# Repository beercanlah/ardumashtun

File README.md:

Ardumashtun
===========

Ardumashtun, an Arduino controlled recirculating mashtun. 

Do you want to improve your home brewing? This projects contains all you need to turn a water heater into a recirculating mash tun. You can find
[more info about our recirculating mash tun](http://beercanlah.com/?page_id=49)
on the blog [beercanlah.com](http://beercanlah.com/).
Here we develop the hard and software that we use to improve our nano brewery.

This repositories contains software for the Arduino. We also provide the eagle cad design design files for the hardware.

Software
------------

We have two different versions of the Arduino sketch that runs our software. One intended for use with an Arduino Uno, and one for use with an Arduino Yun.
When using the Uno you control your mashtun via USB, while the Yun enables you to control your mashtun via the browser.

You can also take a look at the app used for controlling the Uno based mash tun, [kivybrew](https://github.com/beercanlah/kivybrew), and the one controlling the Yun based mash tun, [flapibrew](https://github.com/beercanlah/flapibrew).

Hardware
-------------
Version one of the Ardumashtun hardware is a custom Arduino shield intended to be fabricated by a PCB mill. Recently we have started to migrate towards [Seeedstudios](http://www.seeedstudio.com/) PCB and PCBA service.  We have a running prototype board that only uses parts from the Open Parts Library, so that it can be manufactured using Seeedstudios Fusion PCBA.

License
----------

Unless specifically stated otherwise, everything is licensed under the MIT license, for more information see
LICENSE.txt.

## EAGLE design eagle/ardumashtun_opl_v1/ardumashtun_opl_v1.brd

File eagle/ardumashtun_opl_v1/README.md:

Overview
--------

ardumashtun_opl_v1 is the first attempt to build the mash tun controller using the PCBA service by seeedstudio. 
It works, there are however improvements which we might make in a future version.

Possible Improvements
---------------------

* Label pin header on silk screen
* Add voltage divider on digital pin 0 for use as 3.3 V serial

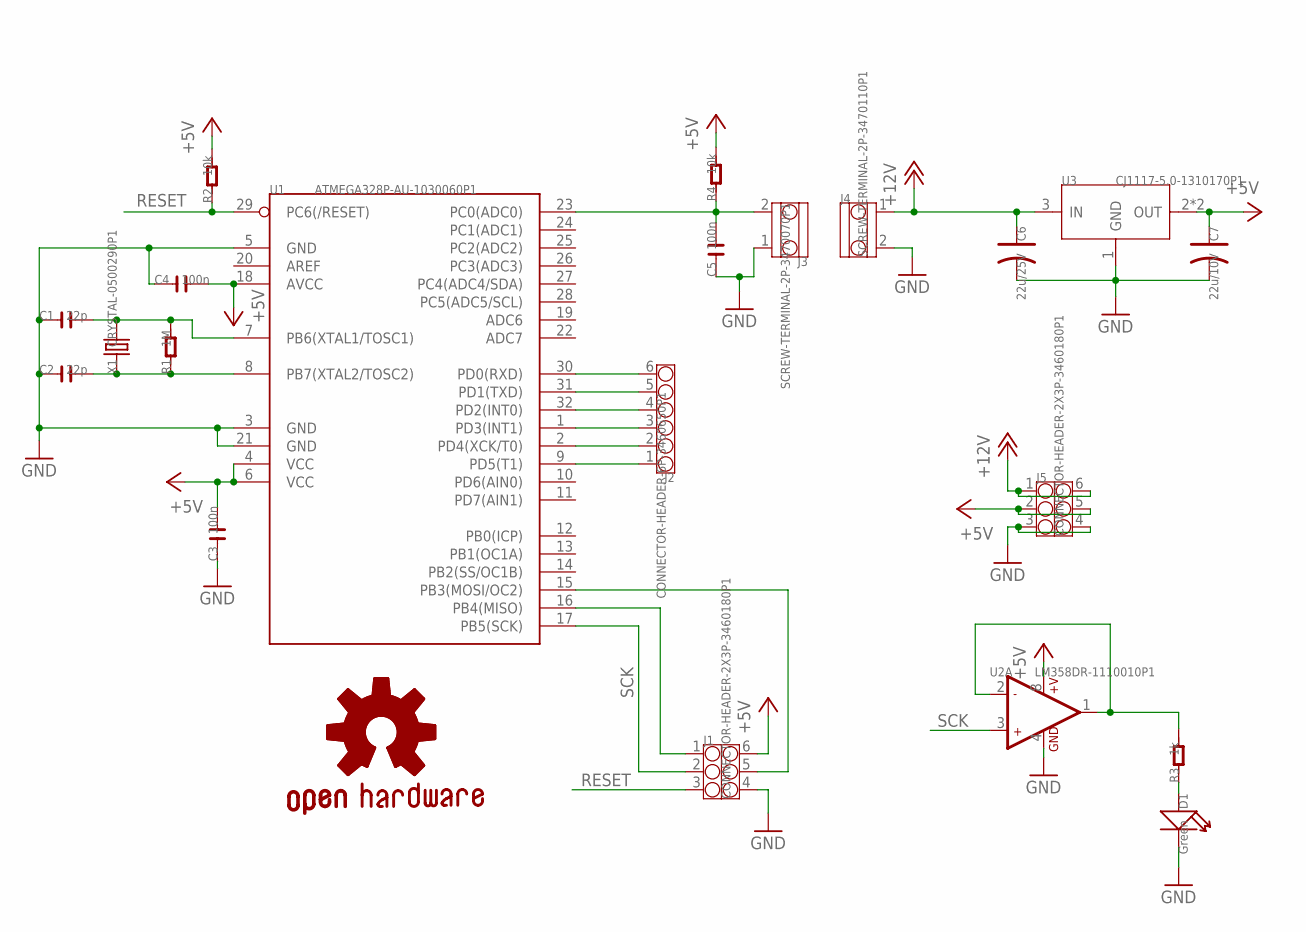
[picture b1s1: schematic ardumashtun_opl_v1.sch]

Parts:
C1, C2: 22p; C0603
C3, C4, C5: 100n; C0603
C6: 22u/25V; AVX-C
C7: 22u/10V; AVX-B
D1: Green; LED0603
GOLD_ORB_SM1: OSHWLOGO_GOLD_ORB_SM; OSHW2
J1, J5: CONNECTOR-HEADER-2X3P-3460180P1; 2X3P-2.54-2.54-11.6-3.0-BLACK-MALE
J2: CONNECTOR-HEADER-6P-3460650P1; 1X6P-2.54-2.54-11.6-3.0-BLACK-MALE
J3: SCREW-TERMINAL-2P-3470070P1; 2P-3.5
J4: SCREW-TERMINAL-2P-3470110P1; 2P-5.0
R1: 1M; R0603
R2, R4: 10k; R0603
R3: 1k; R0603
U1: ATMEGA328P-AU-1030060P1; TQFP32
U2: LM358DR-1110010P1; SOIC8
U3: CJ1117-5.0-1310170P1; SOT223
X1: CRYSTAL-0500290P1; 2P-SMD-5.0X3.2

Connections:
+5V: C3.2, C4.2, C7.+ (1), J1.6, J5.2, J5.5, R2.2, R4.2, U1.4 (VCC), U1.6 (VCC), U1.18 (AVCC), U2.8 (+V), U3.2 (OUT), U3.TER (OUT)
+12V: C6.+ (1), J4.1, J5.1, J5.6, U3.3 (IN)
GND: C1.1, C2.1, C3.1, C4.1, C5.1, C6.- (2), C7.- (2), D1.-, J1.4, J3.1, J4.2, J5.3, J5.4, U1.3 (GND), U1.5 (GND), U1.21 (GND), U2.4 (GND), U3.1 (GND)
unnamed: C1.2, R1.2, U1.7 (PB6(XTAL1/TOSC1)), X1.2
unnamed: C2.2, R1.1, U1.8 (PB7(XTAL2/TOSC2)), X1.1
unnamed: R3.2, U2.1 (OUT1), U2.2 (-IN1)
unnamed: J1.1, U1.16 (PB4(MISO))
unnamed: J1.5, U1.15 (PB3(MOSI/OC2))
unnamed: D1.+, R3.1
unnamed: J2.6, U1.30 (PD0(RXD))
unnamed: J2.5, U1.31 (PD1(TXD))
unnamed: J2.4, U1.32 (PD2(INT0))
unnamed: J2.3, U1.1 (PD3(INT1))
unnamed: J2.2, U1.2 (PD4(XCK/T0))
unnamed: J2.1, U1.9 (PD5(T1))
unnamed: C5.2, J3.2, R4.1, U1.23 (PC0(ADC0))
RESET: J1.3, R2.1, U1.29 (PC6(/RESET))
SCK: J1.2, U1.17 (PB5(SCK)), U2.3 (+IN1)

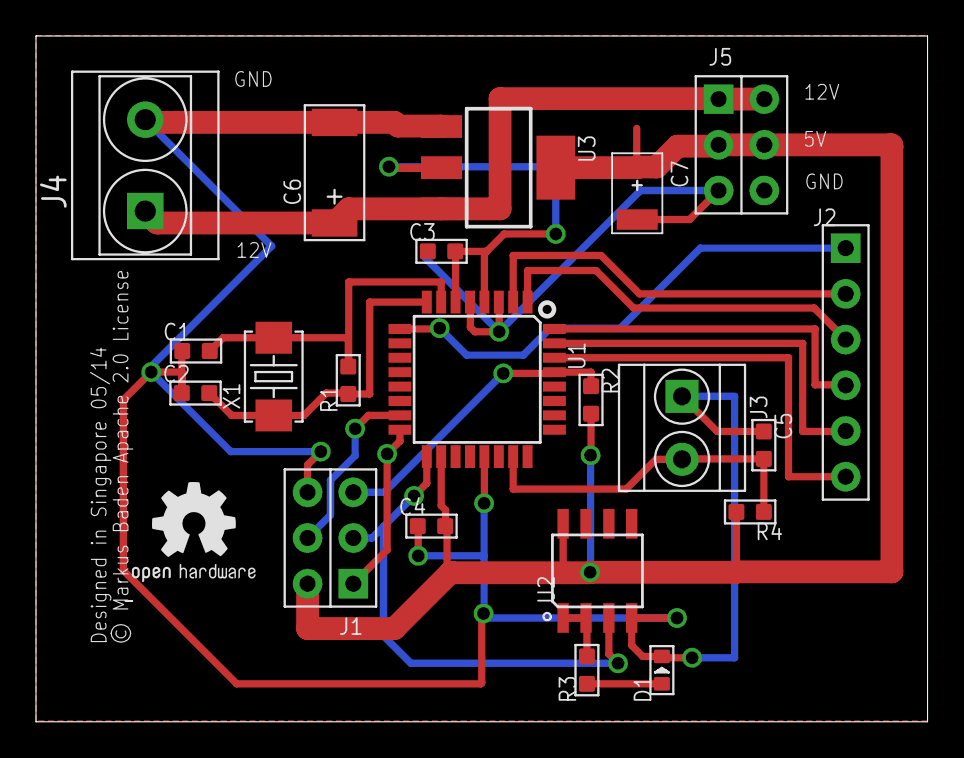
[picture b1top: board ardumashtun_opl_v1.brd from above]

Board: 2 copper layers, 49.5 x 38.1 mm, 22 parts (0 on the bottom side), 18 nets.

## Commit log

2012-01-14 First sketch of zeromq wrapper for serial, that will handle talking to the Arduino
2012-01-22 First version of brew kettle firmware
    Will be based on command parsing since I could not get firmata
    to read analog inputs.
2012-01-22 Pump turns on and off via serial
    Finally got some sort of communications going!
2012-01-23 First script of monitoring temperature committed
2012-01-23 Started class for brew kettle
2012-01-23 Script to monitor temperature now works
2012-01-23 Brew kettle class now controls pump as well
    Monitor temperature script will be used for PID tuning
2012-01-23 refactored echo of readlines
2012-01-23 Monitor temperature script as used for heating measurement
2012-01-23 Have added script to plot data
    Run this in a seperate IPython in order to get
    visual check on things.
2012-01-23 Implemented dutycycle heating
2012-01-23 Further work on duty cycle mode, rewrote brewkettle to parse commands a bit more intelligently. Experimenting with dutycycle mode
2012-01-24 Added way to parse messages using << and defined statements
    Somehow things keep crashing if i put serial inside the if statement...
2012-01-24 Rewrote some of the serial logging, still keeps crashing when serial is inside if statement
2012-01-24 Changed temperature and dutyCycle to be double so that they are compatible with the PID library
2012-01-24 Seems I run out of sram. Commented a lot of log messages. Now can set PID on of
2012-01-24 Added set pid on off to brewekettle.py
2012-01-24 fixed pid on off message cmd id
2012-01-24 Mistake in changing set pid on off cmd id, were correct
2012-01-24 fixed measuretemperature now, void and sets global variabl, error because declared as int
2012-01-24 removed conflicting error messages
2012-01-24 Added setpoint and dutycycle to script
2012-01-24 added function to get input ouput and setpoint
2012-01-24 added input ouput setpoint
2012-01-26 Played some mor ewith zeromq
2012-01-26 Added change setpoint message
2012-01-26 Played with PID parameters, as used for brew
2012-01-26 Added log messages
2012-01-26 arduino sketch as for brew
2012-01-26 brewkettle as for brew
2012-01-26 monitor temperature as for brew
2012-01-26 Removed zeromq files, now in zeromq branch
2012-01-26 Started traits based UI. BrewKettle now inherits from HasTraits
2012-01-26 Setpoint and temperature now default to NaN
2012-01-26 Basic WX App that periodically checks for data implemented
    Taken from https://github.com/enthought/chaco/blob/master/examples/demo/
    advanced/data_stream.py Still closes rather abruptly on exit
2012-01-26 Timer now based on pyface. No more wx, all traitsui based.
2012-01-26 Dummy serial no puts out temperature for testing the app
2012-01-26 Plot of temperature works, after fixing bug in EPD 7.2, see
    https://github.com/enthought/chaco/commit/
    2cb4fd235b928d737b3c244942f8e2e85aa4270d
    and
    https://mail.enthought.com/pipermail/enthought-dev/2012-January/030489.html
2012-01-27 Added timestamp to status message and newly renamed GETALL message
2012-01-27 brewkettle works with new status message
2012-01-27 Reduced timeout in serial communication
2012-01-27 exit from kettle when closing app
2012-01-27 Time now in seconds
2012-01-27 Update the plot manually now works, need to clean py file a lot though
2012-01-27 Cleaned up imports added zoom tool, drawing both at the same time works limits are wrong though
2012-01-27 stopped playing around with overlay plot, can't scale axis... so be it
2012-01-27 Tweaking appearance of views
2012-01-27 Added PID mode flag to get all
2012-01-27 Changed stupid naming getGETALL to getall
2012-01-27 Refactored turning pump on and pump off into seperate function
2012-01-27 Added pump is on flag to get all message
2012-01-27 Added dutycycle and temperature to send to UI
2012-01-27 Added buttons to send updates in setpoint and dutycycle
2012-01-27 Set setpoint now is also set when hitting enter in the text box
2012-01-27 Duty cycle is now also send when hitting enter
2012-01-27 Added buttons to turn PID and pump on and off
2012-01-27 added dutycycle plot
2012-01-27 Added set P and set I methods
2012-01-28 BUG: Pump off checked for wrong condition
2012-01-28 BUG: Added dutycycle to grab current values
2012-01-28 BUG: Fixed additional , in getall reply
2012-01-28 Added check whether data that is grabbed from kettle is new
2012-01-28 Removed debug statement, added check for last timestamp based on floats
2012-01-28 P and I are now sent as float strings and converted by atof
2012-01-29 Added gitignore
2012-01-29 Added data of last brew
2012-01-29 Added good test data
2012-01-29 Added SendableValue class for refactoring the code that generates the view for sending values
2013-01-23 Added test for listing com ports
2013-01-23 Added functionality that one can select the com port and then start communication with the device
2013-02-02 Changed label on comm button
2013-02-02 Made list serial ports work under windows
2013-02-28 Setup py2exe working
2013-09-14 Cleanup: Removed data dir
2013-09-14 Cleanup: Removed test script for serial port selection
2013-09-14 Cleanup: Removed temperature monitor script
2013-09-14 Licensed project under MIT license
2013-09-14 Removed setup.py, now in seperate branch
2013-09-14 Cleanup removed helper script
2013-09-14 Added fake port for testing
2013-09-14 Moved python to subdirectory
2013-09-14 Added eagle schematics and board
2013-09-14 Renamed eagle files
2013-09-14 Added readme for whole project
2013-09-14 Added link to blog
2014-02-15 Copied brew kettle to convert it for Yun
2014-02-15 Removed yun directory from master
    Development will be done in seperate branch
2014-02-16 Started rewrite of sketch, not compiling yet
2014-02-16 Got basic version compiling
2014-02-16 Added trim after command
    Now the sequence of readStringUntil('/') and trim() will map commands
    correctly.
2014-02-16 Got skeleton function for all commands, compiles, not verified yet
2014-02-16 Removed streaming stuff (<<) and unused libraries
2014-02-16 pyflake changes to brew kettle
2014-02-18 Added hello world from scipy cookbook
2014-02-18 Added emacs temp files to gitgignore
2014-02-18 Renamed wxgui folder to yungui
2014-02-22 Added notebook to test yun
2014-02-25 Played around with hello world
2014-02-25 Status now via /data/get
    All set functions now use Bridge.put() to communicate status
    The process functions no longer return anything via http
2014-02-27 More changes to yun to work with flapibrew
2014-05-17 Removed obsolete messaging
2014-05-17 Arduino communicates via CmdMessenger 3.5
2014-05-17 Arduino responds to temperature request
2014-05-17 Removed old python script based on old message specs
2014-05-17 Renamed brew_kettle to uno_mashtun
2014-05-17 Rename brew_kettle_yun to yun_mashtun
2014-05-17 Removed yungui (obsolete)
2014-05-17 Started python file to control mashtun
2014-05-17 Python class now reads in temperature
2014-05-17 Added test script for uno
2014-05-17 Uno now communicates pump status
2014-05-17 Uno now turns pump on and off
2014-05-17 Uno now communicates heater status
2014-05-17 Added dutycyle message
2014-05-17 Message numbers no longer hard coded
2014-05-17 Added dutyCycleStatus message
2014-05-17 Uno now reports dutycycle
2014-05-17 Can now control uno's dutycycle
2014-05-17 Uno reports pid status
2014-05-17 Removed kHeater as heater is not settable
2014-05-17 Can control pidstate
2014-05-17 Added setpointStatus
2014-05-17 Uno reports setpoint now
2014-05-17 Uno can set setpoing now
2014-05-17 Added kPValueStatus and kIValueStatus
2014-05-17 Uno reports p and i value
2014-05-17 Uno can change P and I value
2014-05-18 Factor writing to serial from msg
2014-05-18 Started unittests
    Renamed test script to validate to make sure it won't be discovered as
    as a test.
2014-05-18 Tests runs (no tests yet)
2014-05-18 First test failes successfully
2014-05-18 Got first mock to passed
2014-05-18 Added pump test
2014-05-18 Refactored message assertation
2014-05-18 Test for every message
2014-05-18 Fixed kDutyCycle handling
2014-05-18 Removed printing of messages now that there are some tests
2014-05-18 Unit test for reading temperature works
2014-05-18 Temperature read correctly from Uno
2014-05-18 Unittest for pump passes
2014-05-18 Added one more pump test
2014-05-18 Pump is validated on Uno
2014-05-18 Validated heater, unit test dutycycle
2014-05-18 Validated dutycyle
2014-05-18 Validated and unit tested the rest
2014-06-08 Moved board v1 to separate folder
2014-06-08 Test board using the Open Parts Library added
    The board uses only parts from Seeedstudio's open parts library and
    can be manufactured by the Fusion PCBA service.
2014-06-08 Added eagle files to gitignore
    Curtesy of https://github.com/github/gitignore/blob/master/Eagle.gitignore
2014-06-08 Added links for kivybrew and flapibrew to readme
2014-06-12 Started documenting opl version
2018-12-16 Updated to python 3

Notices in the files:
eagle/ardumashtun_opl_v1/ardumashtun_opl_v1.brd:
© Markus Baden Apache 2.0 License
